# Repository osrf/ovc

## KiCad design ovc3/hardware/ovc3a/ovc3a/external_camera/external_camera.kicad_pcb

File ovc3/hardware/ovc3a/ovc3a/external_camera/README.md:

# Lens holders
Lens holders have 20mm spacing. There are various options that work fine.
We have used PT-LH010M from m12lenses.com with good results:
https://www.m12lenses.com/CNC-Machined-M12-Lens-Holder-Metal-p/pt-lh010m.htm

# FFC jumpers
The required length of jumper depends on how the external-camera board is
mounted with respect to the main OVC3 board. We have used Molex 15266-0281
for 6" length (about 150mm) but many other alternatives are possible.

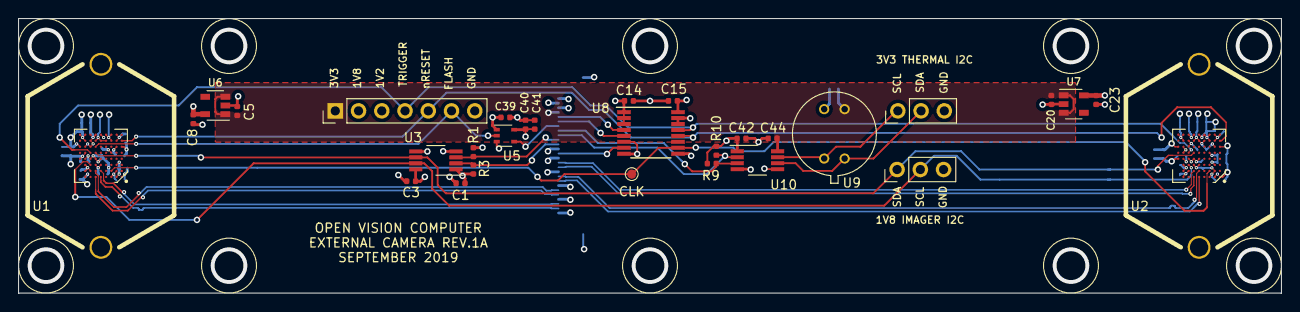
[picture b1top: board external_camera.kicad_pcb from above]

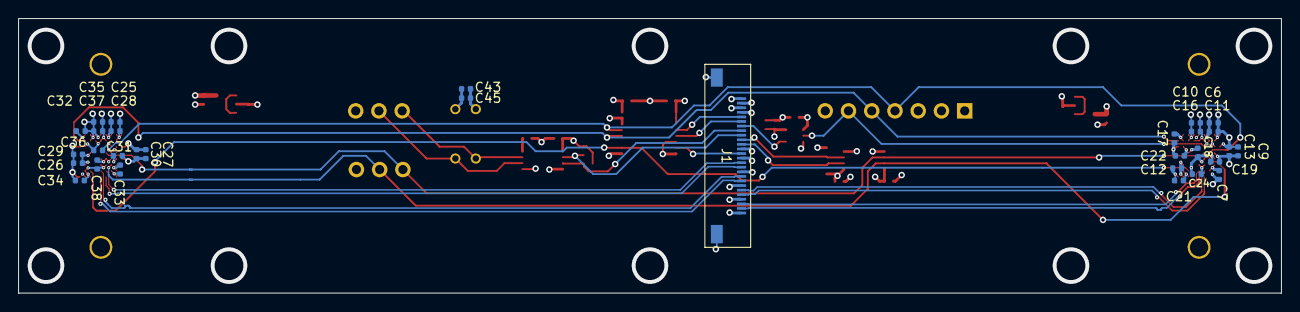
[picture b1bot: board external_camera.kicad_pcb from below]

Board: 6 copper layers, 138.0 x 30.0 mm, 63 parts (31 on the bottom side), 30 nets.

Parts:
C1, C3, C11, C12, C13, C14, C15, C16, C17, C18, C19, C21, C22, C24, C28, C29, C30, C32, C33, C34, C35, C36, C37, C38, C39, C40, C42, C43, C44: 100n; C_0402_1005Metric
C5, C8, C20, C23, C45: 1u; C_0402_1005Metric
C6, C7, C9, C10, C25, C26, C27, C31, C41: 10u; C_0402_1005Metric
J1: FFC; MOLEX_505110_2691
J2, J3: DNP; LENS_HOLDER_20MM_PT-LH010M
J4: DNP; PinHeader_1x07_P2.54mm_Vertical
J5, J6: DNP; PinHeader_1x03_P2.54mm_Vertical
R1, R3: 2k2; R_0402_1005Metric
R9, R10: DNP; R_0402_1005Metric
TP1: DNP; TestPoint_Pad_D1.0mm
U1, U2: AR0144CS; BGA-72_9x8_5.545x5.565mm
U3, U10: TCA9803; VSSOP-8_3.0x3.0mm_P0.65mm
U5: SN74AUP1T34DCK; SOT-353_SC-70-5
U6, U7: LP5907MFX-2.8; SOT-23-5
U8: SN74AXC4T245PWR; TSSOP-16_4.4x5mm_P0.65mm
U9: DNP; Melexis_TO-39

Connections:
+1V2: C1.1, C10.1, C14.1, C16.1, C19.1, C21.1, C22.1, C24.1, C31.1, C34.1, C35.1, C36.1, C37.1, C38.1, C40.1, C41.1, C42.1, J1.2, J4.3, R1.1, R3.1, R9.1, R10.1, U1.A3, U1.B2, U1.C5, U1.C6, U1.D8, U1.F2, U1.G4, U1.G5, U1.G6, U2.A3, U2.B2, U2.C5, U2.C6, U2.D8, U2.F2, U2.G4, U2.G5, U2.G6, U3.1, U3.5, U5.5, U8.1, U8.2, U8.3, U10.1, U10.5
+1V8: C3.1, C7.1, C12.1, C15.1, C18.1, C26.1, C29.1, C33.1, C39.1, J1.3, J4.2, U1.A2, U1.B7, U1.B8, U1.C2, U1.C8, U1.E3, U2.A2, U2.B8, U2.C2, U2.C8, U2.E3, U3.8, U5.1, U8.16
+3V3: C5.1, C20.1, C43.1, C44.1, C45.1, J1.4, J4.1, U6.1, U6.3, U7.1, U7.3, U9.2, U10.8
/CAM0_2V8: C6.1, C8.1, C9.1, C11.1, C13.1, C17.1, U1.F9, U1.G2, U1.G8, U1.H1, U1.H2, U1.H8, U1.H9, U6.5
/CAM1_2V8: C23.1, C25.1, C27.1, C28.1, C30.1, C32.1, U2.F9, U2.G2, U2.G8, U2.H1, U2.H2, U2.H8, U2.H9, U7.5
/EXTCLK_1V2: J1.13, U8.7
/EXTCLK_1V8: TP1.1, U1.B3, U2.B3, U8.10
/FLASH_1V2: J1.7, U5.4
/FLASH_1V8: J4.6, U1.F6, U5.2
/MIPI_CLK0+: J1.25, U1.A5
/MIPI_CLK0-: J1.24, U1.B5
/MIPI_CLK1+: J1.19, U2.A5
/MIPI_CLK1-: J1.18, U2.B5
/MIPI_DAT0+: J1.22, U1.A6
/MIPI_DAT0-: J1.21, U1.B6
/MIPI_DAT1+: J1.16, U2.A6
/MIPI_DAT1-: J1.15, U2.B6
/RESET_1V2: J1.6, U8.5
/RESET_1V8: J4.5, U1.G1, U2.G1, U8.12
/SCL0_1V2: J1.11, R3.2, U3.2
/SCL0_1V8: J5.2, U1.C7, U2.C7, U3.7
/SCL1_1V2: J1.9, R10.2, U10.2
/SCL1_3V3: J6.1, U9.4, U10.7
/SDA0_1V2: J1.10, R1.2, U3.3
/SDA0_1V8: J5.1, U1.E6, U2.E6, U3.6
/SDA1_1V2: J1.8, R9.2, U10.3
/SDA1_3V3: J6.2, U9.1, U10.6
/TRIGGER_1V2: J1.5, U8.4
/TRIGGER_1V8: J4.4, U1.E7, U2.E7, U8.13
GND: C1.2, C3.2, C5.2, C6.2, C7.2, C8.2, C9.2, C10.2, C11.2, C12.2, C13.2, C14.2, C15.2, C16.2, C17.2, C18.2, C19.2, C20.2, C21.2, C22.2, C23.2, C24.2, C25.2, C26.2, C27.2, C28.2, C29.2, C30.2, C31.2, C32.2, C33.2, C34.2, C35.2, C36.2, C37.2, C38.2, C39.2, C40.2, C41.2, C42.2, C43.2, C44.2, C45.2, J1.1, J1.12, J1.14, J1.17, J1.20, J1.23, J1.26, J1.27, J2.1, J3.1, J4.7, J5.3, J6.3, U1.A1, U1.A8, U1.D5, U1.D6, U1.D7, U1.D9, U1.E8, U1.F1, U1.F7, U1.F8, U1.G3, U1.G7, U1.H3, U1.H4, U1.H5, U1.H6, U1.H7, U2.A1, U2.A8, U2.B7, U2.D5, U2.D6, U2.D7, U2.D9, U2.E8, U2.F1, U2.F7, U2.F8, U2.G3, U2.G7, U2.H3, U2.H4, U2.H5, U2.H6, U2.H7, U3.4, U5.3, U6.2, U7.2, U8.6, U8.8, U8.9, U8.14, U8.15, U9.3, U10.4

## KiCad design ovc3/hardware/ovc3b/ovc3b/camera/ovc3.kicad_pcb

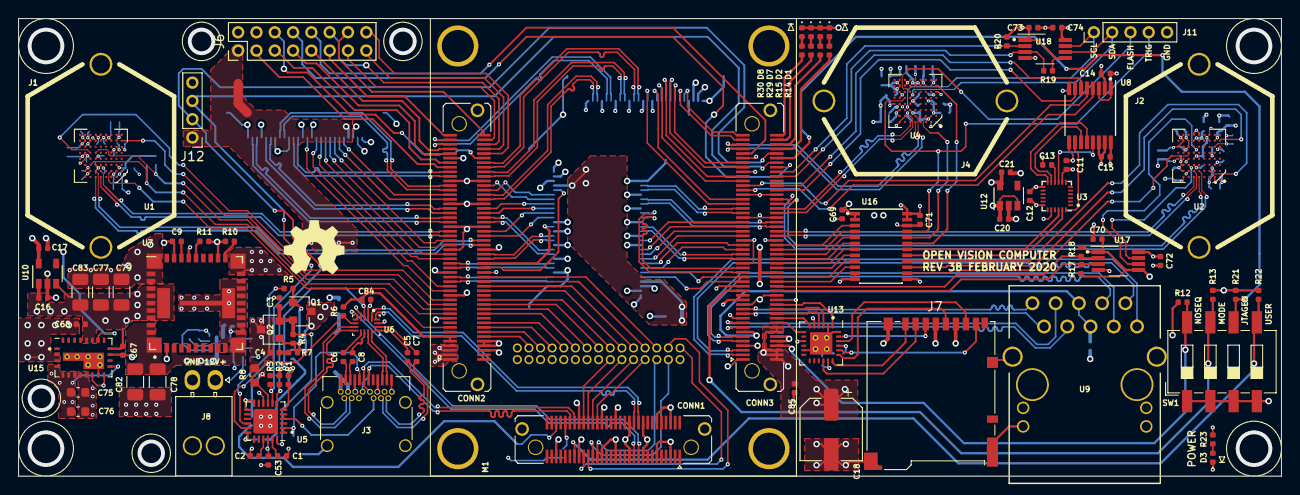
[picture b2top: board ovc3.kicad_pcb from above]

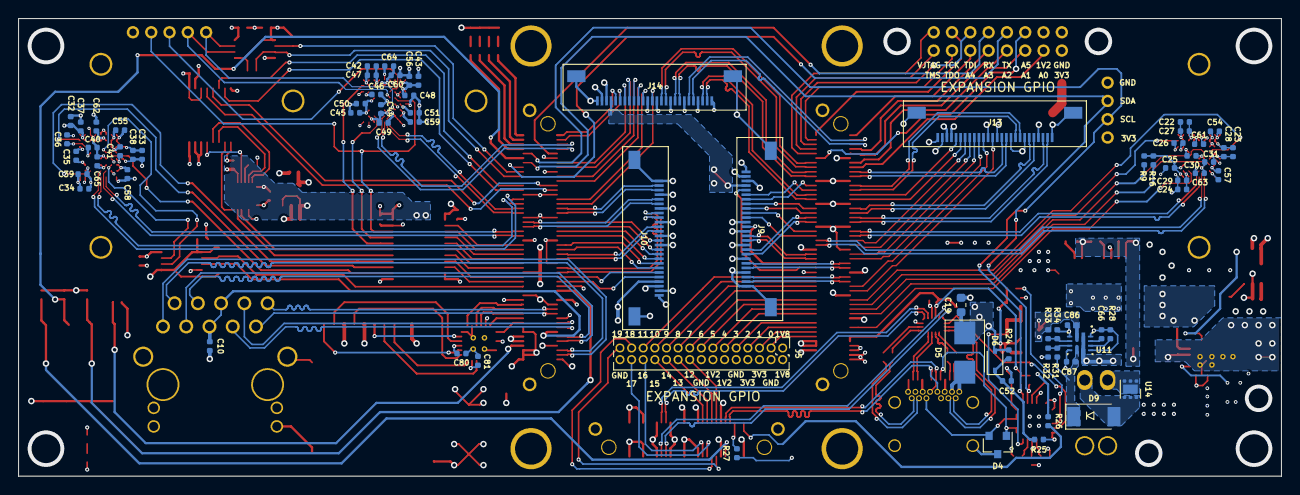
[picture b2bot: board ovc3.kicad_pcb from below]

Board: 6 copper layers, 138.0 x 50.0 mm, 167 parts (72 on the bottom side), 238 nets.

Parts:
C1, C2, C3, C16, C17, C20, C21, C52, C67: 1u; C_0402_1005Metric
C4, C5, C6, C7, C8, C10, C11, C12, C13, C14, C15, C26, C27, C28, C29, C30, C31, C36, C37, C38, C39, C40, C41, C44, C47, C48, C49, C50, C51, C53, C54, C55, C56, C57, C58, C59, C60, C61, C62, C63, C64, C65, C66, C69, C70, C71, C72, C73, C74, C80, C81, C84, C85, C86, C87: 100n; C_0402_1005Metric
C9: 3n3; C_0402_1005Metric
C18: 680u; CP_Elec_6.3x7.7
C19: 4u7; C_0603_1608Metric
C22, C23, C24, C25, C32, C33, C34, C35, C42, C43, C45, C46, C68: 10u; C_0402_1005Metric
C75, C76: 22u; C_0603_1608Metric
C77: 100u; C_1206_3216Metric
C78, C82: 22u; C_1206_3216Metric
C79, C83: 47u; C_1206_3216Metric
D1, D2, D3, D7, D8: LED; LED_0402_1005Metric
D4: ESD7002WTT1G; SOT-23
D5: SMBJ22A; D_SMB
D6: SDMK0340L-7-F; D_SOD-323
D9: PMEG3030EP,115; D_SOD-128
J1: LEFT_LENS; LENS_HOLDER_20MM_PT-LH010M
J2: RIGHT_LENS; LENS_HOLDER_20MM_PT-LH010M
J3: USB_C_Receptacle; USB_C_Receptacle_Wurth_632723300011
J4: MIDDLE_LENS; LENS_HOLDER_20MM_PT-LH010M
J5: LOW_SPEED_EXP; PinHeader_2x15_P1.27mm_Vertical
J6: FRONT_PACK; PinHeader_2x08_P2.00mm_Vertical
J7: Micro_SD_Card_Det_Hirose_DM3BT; microSD_HC_Hirose_DM3BT-DSF-PEJS
J8: AUX_PWR; Molex_Nano-Fit_105313-xx02_1x02_P2.50mm_Horizontal
J9: BONUS1; MOLEX_505110_2691
J10: BONUS2; MOLEX_505110_2691
J11: CAM2_TIMING_DEBUG; PinHeader_1x05_P2.00mm_Vertical
J12: I2C_DEBUG; PinHeader_1x04_P2.00mm_Vertical
J13: BONUS3; MOLEX_505110_2691
J14: BONUS4; MOLEX_505110_2691
LOGO1: Logo_Open_Hardware_Small; OSHW-Symbol_6.7x6mm_SilkScreen
M1: TE0820
Q1, Q2: SI2369DS; SOT-23
R1, R4, R6: 100k; R_0402_1005Metric
R2, R3, R12, R13, R21, R22, R26, R32, R34: 10k; R_0402_1005Metric
R5, R28: 22k; R_0402_1005Metric
R7: 100R; R_0402_1005Metric
R8: 1k; R_0603_1608Metric
R9, R16, R17, R18, R19, R20: 2k2; R_0402_1005Metric
R10: 90k9; R_0402_1005Metric
R11: 316R; R_0402_1005Metric
R14, R15, R23, R29, R30: 330R; R_0402_1005Metric
R24: 470; R_0402_1005Metric
R25, R27: 1k; R_0402_1005Metric
R31, R33: 143k; R_0402_1005Metric
SW1: SW_DIP_x04; SW_DIP_SPSTx04_Slide_6.7x11.72mm_W8.61mm_P2.54mm_LowProfile
U1, U2, U4: AR0144CS; BGA-72_9x8_5.545x5.565mm
U3: ICM-20948; InvenSense_QFN-24_3x3mm_P0.4mm
U5: STUSB4500; QFN-24-1EP_4x4mm_P0.5mm_EP2.7x2.7mm
U6: HD3SS3202; TI_R_PUQFN_N16
U7: LMZ31707; TI_RVQ_42
U8: SN74AXC4T245; TSSOP-16_4.4x5mm_P0.65mm
U9: ARJ11C-MBSAS-A-BA-7MU2
U10, U12: LP5907MFX-2.8; SOT-23-5
U11: TPS2121; Texas_VQFN-HR-12_2x2.5_Pitch0.5mm
U13: TXS02612; TI_RTW0024B
U14: TVS1800DRV; WSON-6-1EP_2x2mm_P0.65mm_EP1x1.6mm
U15: EN5322QI; Converter_DCDC_Intel_QFN-24_4x6mm_P0.65mm_ThermalVias
U16: SN74AXCH8T245; TSSOP-24_4.4x7.8mm_P0.65mm
U17, U18: TCA9803; VSSOP-8_3.0x3.0mm_P0.65mm

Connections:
3V3_VOUT: C84.2, M1.JB2.9, M1.JB2.11, R2.1, R3.1, R6.1, U6.3
+1V2: C14.1, C24.1, C26.1, C29.1, C31.1, C34.1, C36.1, C39.1, C41.1, C44.1, C46.1, C49.1, C51.1, C60.1, C61.1, C62.1, C63.1, C64.1, C65.1, C69.1, C70.1, C73.1, C75.1, C76.1, J5.12, J5.14, J6.4, J9.25, J10.25, J13.25, J14.25, M1.JB1.10, M1.JB1.12, M1.JB2.8, M1.JB2.10, R17.1, R18.1, R19.1, R20.1, U1.A3, U1.B2, U1.C5, U1.C6, U1.D8, U1.F2, U1.G4, U1.G5, U1.G6, U2.A3, U2.B2, U2.C5, U2.C6, U2.D8, U2.F2, U2.G4, U2.G5, U2.G6, U4.A3, U4.B2, U4.C5, U4.C6, U4.D8, U4.F2, U4.G4, U4.G5, U4.G6, U8.1, U8.3, U15.4, U15.5, U15.6, U15.7, U15.13, U16.1, U16.2, U17.1, U17.5, U18.1, U18.5
+1V8: C11.1, C15.1, C25.1, C30.1, C35.1, C40.1, C45.1, C50.1, C57.1, C58.1, C59.1, C71.1, C72.1, C74.1, J5.1, J5.2, J9.24, J10.24, J13.24, J14.24, M1.JB1.40, M1.JB2.6, R9.1, R13.1, R16.1, R21.1, R22.1, U1.A2, U1.B8, U1.C2, U1.C8, U1.E3, U2.A2, U2.B8, U2.C2, U2.C8, U2.E3, U3.8, U4.A2, U4.B8, U4.C2, U4.C8, U4.E3, U8.16, U15.18, U16.23, U16.24, U17.8, U18.8
+3V3: C12.1, C16.1, C18.1, C20.1, C53.1, C67.1, C68.1, C77.1, C79.1, C80.1, C81.1, C83.1, C85.1, J5.6, J5.8, J6.1, J7.4, J9.23, J10.23, J12.1, J13.23, J14.23, M1.JB1.2, M1.JB1.4, M1.JB1.6, M1.JB1.14, M1.JB1.16, M1.JB1.27, M1.JB2.1, M1.JB2.3, M1.JB2.5, M1.JB2.7, R12.1, R23.1, R27.1, U3.13, U5.22, U7.27, U7.34, U7.35, U7.36, U7.37, U7.38, U7.41, U10.1, U10.3, U12.1, U12.3, U13.5, U13.17, U13.21, U15.10, U15.12, U15.16, U15.19, U15.20
/imagers/CAM0_2V8: C17.1, C22.1, C23.1, C27.1, C28.1, C54.1, U1.F9, U1.G2, U1.G8, U1.H1, U1.H2, U1.H8, U1.H9, U10.5
/imagers/CAM1_2V8: C21.1, C32.1, C33.1, C37.1, C38.1, C42.1, C43.1, C47.1, C48.1, C55.1, C56.1, U2.F9, U2.G2, U2.G8, U2.H1, U2.H2, U2.H8, U2.H9, U4.F9, U4.G2, U4.G8, U4.H1, U4.H2, U4.H8, U4.H9, U12.5
/misc/LS_CLK: J7.5, U13.19
/misc/LS_CMD: J7.3, U13.23
/misc/LS_DAT0: J7.7, U13.22
/misc/LS_DAT1: J7.8, U13.20
/misc/LS_DAT2: J7.1, U13.18
/misc/LS_DAT3: J7.2, U13.16
/te0820/CAM1_EXTCLK_1V2: M1.JB1.42, U16.8
/te0820/CAM1_SCL_1V2: M1.JB1.34, R18.2, U17.2
/te0820/CAM1_SDA_1V2: M1.JB1.32, R17.2, U17.3
/te0820/CAM1_TRIG_1V2: M1.JB1.36, U16.10
/te0820/CAM1_nRESET_1V2: M1.JB1.38, U16.9
/te0820/CAM2_EXTCLK_1V2: M1.JB1.50, U16.4
/te0820/CAM2_SCL_1V2: M1.JB1.84, R20.2, U18.2
/te0820/CAM2_SDA_1V2: M1.JB1.82, R19.2, U18.3
/te0820/CAM2_TRIG_1V2: M1.JB1.52, U16.3
/te0820/CAM2_nRESET_1V2: M1.JB1.48, U16.5
/te0820/DIPSWITCH: M1.JB3.47, R22.2, SW1.5
/te0820/ICM_IMU_INT1_1V2: M1.JB1.77, U8.5
/te0820/ICM_SPI_CLK_1V2: M1.JB1.44, U16.7
/te0820/ICM_SPI_CS_1V2: M1.JB1.46, U16.6
/te0820/ICM_SPI_MISO_1V2: M1.JB1.75, U8.4
/te0820/ICM_SPI_MOSI_1V2: M1.JB1.76, U8.7
/te0820/ICM_SPI_SYNC_1V2: M1.JB1.78, U8.6
/te0820/JTAGEN: M1.JB1.90, R21.2, SW1.6
/te0820/MODE: M1.JB1.31, R13.2, SW1.7
/te0820/NOSEQ: M1.JB1.8, R12.2, SW1.8
/usb3/1V2: C2.1, U5.21
/usb3/2V7: C1.1, U5.23
/usb3/ABSIDE: R6.2, U5.17, U6.6
/usb3/AUX_PWR: D9.2, J8.1, U14.4, U14.5, U14.6
/usb3/CONN_CC1: D4.1, J3.A5, U5.1, U5.2
/usb3/CONN_CC2: D4.2, J3.B5, U5.4, U5.5
/usb3/CONN_RX1+: J3.B11, U6.8
/usb3/CONN_RX1-: J3.B10, U6.7
/usb3/CONN_RX2+: J3.A11, U6.12
/usb3/CONN_RX2-: J3.A10, U6.11
/usb3/CONN_TX1+: C6.2, J3.A2
/usb3/CONN_TX1-: C8.2, J3.A3
/usb3/CONN_TX2+: C5.2, J3.B2
/usb3/CONN_TX2-: C7.2, J3.B3
/usb3/CONN_VBUS: C19.1, D5.1, D6.2, J3.A4, J3.A9, J3.B4, J3.B9, Q1.3, R24.1
/usb3/DISCH: R8.2, U5.9
/usb3/GATES: Q1.1, Q2.1, R4.2, R5.1, R7.2
/usb3/PH: U7.10, U7.13, U7.14, U7.15, U7.16, U7.17, U7.18, U7.19, U7.42
/usb3/PWGND: C9.2, R10.2, R11.2, U7.2, U7.23, U7.29
/usb3/RESET: R1.1, U5.6
/usb3/T1+: C6.1, U6.9
/usb3/T1-: C8.1, U6.10
/usb3/T2+: C5.1, U6.13
/usb3/T2-: C7.1, U6.14
/usb3/VAUX: C87.1, D9.1, R31.1, U11.7
BONUS1_CLK0+: J9.2, M1.JB2.35
BONUS1_CLK0-: J9.3, M1.JB2.37
BONUS1_CLK1+: J9.8, M1.JB2.62
BONUS1_CLK1-: J9.9, M1.JB2.64
BONUS1_DAT0+: J9.5, M1.JB2.41
BONUS1_DAT0-: J9.6, M1.JB2.43
BONUS1_DAT1+: J9.11, M1.JB2.46
BONUS1_DAT1-: J9.12, M1.JB2.48
BONUS1_EXTCLK: J9.14, M1.JB2.44
BONUS1_FLASH: J9.20, M1.JB2.78
BONUS1_RESET: J9.21, M1.JB2.76
BONUS1_SCL0: J9.16, M1.JB2.56
BONUS1_SCL1: J9.18, M1.JB2.66
BONUS1_SDA0: J9.17, M1.JB2.58
BONUS1_SDA1: J9.19, M1.JB2.68
BONUS1_TRIGGER: J9.22, M1.JB2.42
BONUS2_CLK0+: J10.2, M1.JB1.67
BONUS2_CLK0-: J10.3, M1.JB1.65
BONUS2_CLK1+: J10.8, M1.JB1.39
BONUS2_CLK1-: J10.9, M1.JB1.41
BONUS2_DAT0+: J10.5, M1.JB1.62
BONUS2_DAT0-: J10.6, M1.JB1.60
BONUS2_DAT1+: J10.11, M1.JB1.47
BONUS2_DAT1-: J10.12, M1.JB1.45
BONUS2_EXTCLK: J10.14, M1.JB1.61
BONUS2_FLASH: J10.20, M1.JB1.49
BONUS2_RESET: J10.21, M1.JB1.37
BONUS2_SCL0: J10.16, M1.JB1.59
BONUS2_SCL1: J10.18, M1.JB1.55
BONUS2_SDA0: J10.17, M1.JB1.57
BONUS2_SDA1: J10.19, M1.JB1.51
BONUS2_TRIGGER: J10.22, M1.JB1.35
BONUS3_CLK0+: J13.2, M1.JB2.61
BONUS3_CLK0-: J13.3, M1.JB2.63
BONUS3_CLK1+: J13.8, M1.JB2.77
BONUS3_CLK1-: J13.9, M1.JB2.75
BONUS3_DAT0+: J13.5, M1.JB2.65
BONUS3_DAT0-: J13.6, M1.JB2.67
BONUS3_DAT1+: J13.11, M1.JB2.81
BONUS3_DAT1-: J13.12, M1.JB2.83
BONUS3_EXTCLK: J13.14, M1.JB2.31
BONUS3_FLASH: J13.20, M1.JB2.53
BONUS3_RESET: J13.21, M1.JB2.71
BONUS3_SCL0: J13.16, M1.JB2.33
BONUS3_SCL1: J13.18, M1.JB2.47
BONUS3_SDA0: J13.17, M1.JB2.45
BONUS3_SDA1: J13.19, M1.JB2.51
BONUS3_TRIGGER: J13.22, M1.JB2.73
BONUS4_CLK0+: J14.2, M1.JB2.72
BONUS4_CLK0-: J14.3, M1.JB2.74
BONUS4_CLK1+: J14.8, M1.JB2.82
BONUS4_CLK1-: J14.9, M1.JB2.84
BONUS4_DAT0+: J14.5, M1.JB2.95
BONUS4_DAT0-: J14.6, M1.JB2.97
BONUS4_DAT1+: J14.11, M1.JB2.86
BONUS4_DAT1-: J14.12, M1.JB2.88
BONUS4_EXTCLK: J14.14, M1.JB1.69
BONUS4_FLASH: J14.20, M1.JB1.87
BONUS4_RESET: J14.21, M1.JB1.97
BONUS4_SCL0: J14.16, M1.JB1.71
BONUS4_SCL1: J14.18, M1.JB1.81
BONUS4_SDA0: J14.17, M1.JB1.79
BONUS4_SDA1: J14.19, M1.JB1.85
BONUS4_TRIGGER: J14.22, M1.JB1.99
CAM0_CLK+: M1.JB2.55, U1.A5
CAM0_CLK-: M1.JB2.57, U1.B5
CAM0_D0+: M1.JB2.52, U1.A6
CAM0_D0-: M1.JB2.54, U1.B6
CAM0_EXTCLK_1V8: M1.JB2.15, U1.B3
CAM0_SCL_1V8: M1.JB2.21, R16.2, U1.C7
CAM0_SDA_1V8: M1.JB2.23, R9.2, U1.E6
CAM0_TRIG_1V8: M1.JB2.27, U1.E7
CAM0_nRESET_1V8: M1.JB2.25, U1.G1
CAM1_CLK+: M1.JB1.70, U2.A5
CAM1_CLK-: M1.JB1.72, U2.B5
CAM1_D0+: M1.JB1.58, U2.A6
CAM1_D0-: M1.JB1.56, U2.B6
CAM1_EXTCLK_1V8: U2.B3, U16.16
CAM1_SCL_1V8: U2.C7, U17.7
CAM1_SDA_1V8: U2.E6, U17.6
CAM1_TRIG_1V8: U2.E7, U16.14
CAM1_nRESET_1V8: U2.G1, U16.15
CAM2_CLK+: M1.JB1.95, U4.A5
CAM2_CLK-: M1.JB1.93, U4.B5
CAM2_D0+: M1.JB1.68, U4.A6
CAM2_D0-: M1.JB1.66, U4.B6
CAM2_EXTCLK_1V8: U4.B3, U16.20
CAM2_FLASH_1V8: J11.3, U4.F6
CAM2_SCL_1V8: J11.1, U4.C7, U18.7
CAM2_SDA_1V8: J11.2, U4.E6, U18.6
CAM2_TRIG_1V8: J11.4, U4.E7, U16.21
CAM2_nRESET_1V8: U4.G1, U16.19
ETH_VCC: C10.1, M1.JB1.13, U9.5, U9.6
FRONT_AUX0: J6.3, M1.JB2.85
FRONT_AUX1: J6.5, M1.JB2.87
FRONT_AUX2: J6.7, M1.JB2.91
FRONT_AUX3: J6.9, M1.JB2.93
FRONT_AUX4: J6.11, M1.JB2.99
FRONT_AUX5: J6.6, M1.JB2.90
GND: C1.2, C2.2, C3.2, C10.2, C11.2, C12.2, C13.2, C14.2, C15.2, C16.2, C17.2, C18.2, C19.2, C20.2, C21.2, C22.2, C23.2, C24.2, C25.2, C26.2, C27.2, C28.2, C29.2, C30.2, C31.2, C32.2, C33.2, C34.2, C35.2, C36.2, C37.2, C38.2, C39.2, C40.2, C41.2, C42.2, C43.2, C44.2, C45.2, C46.2, C47.2, C48.2, C49.2, C50.2, C51.2, C52.2, C53.2, C54.2, C55.2, C56.2, C57.2, C58.2, C59.2, C60.2, C61.2, C62.2, C63.2, C64.2, C65.2, C66.2, C67.2, C68.2, C69.2, C70.2, C71.2, C72.2, C73.2, C74.2, C75.2, C76.2, C77.2, C78.2, C79.2, C80.2, C81.2, C82.2, C83.2, C84.1, C85.2, C86.2, C87.2, D1.1, D2.1, D3.1, D4.3, D5.2, D7.1, D8.1, J1.1, J2.1, J3.A1, J3.A12, J3.B1, J3.B12, J3.S1, J4.1, J5.4, J5.10, J5.16, J5.30, J6.2, J7.6, J7.11, J8.2, J9.1, J9.4, J9.7, J9.10, J9.13, J9.15, J9.26, J9.27, J10.1, J10.4, J10.7, J10.10, J10.13, J10.15, J10.26, J10.27, J11.5, J12.4, J13.1, J13.4, J13.7, J13.10, J13.13, J13.15, J13.26, J13.27, J14.1, J14.4, J14.7, J14.10, J14.13, J14.15, J14.26, J14.27, M1.JB1.1, M1.JB1.7, M1.JB1.19, M1.JB1.25, M1.JB1.30, M1.JB1.33, M1.JB1.43, M1.JB1.53, M1.JB1.54, M1.JB1.63, M1.JB1.64, M1.JB1.73, M1.JB1.74, M1.JB1.83, M1.JB1.89, M1.JB2.19, M1.JB2.29, M1.JB2.39, M1.JB2.40, M1.JB2.49, M1.JB2.50, M1.JB2.59, M1.JB2.60, M1.JB2.69, M1.JB2.70, M1.JB2.79, M1.JB2.80, M1.JB2.89, M1.JB3.5, M1.JB3.6, M1.JB3.11, M1.JB3.12, M1.JB3.17, M1.JB3.18, M1.JB3.23, M1.JB3.24, M1.JB3.29, M1.JB3.30, M1.JB3.35, M1.JB3.36, M1.JB3.45, M1.JB3.46, M1.JB3.55, R1.2, R28.2, R32.2, R34.2, SW1.1, SW1.2, SW1.3, SW1.4, U1.A1, U1.A8, U1.B7, U1.D5, U1.D6, U1.D7, U1.D9, U1.E8, U1.F1, U1.F7, U1.F8, U1.G3, U1.G7, U1.H3, U1.H4, U1.H5, U1.H6, U1.H7, U2.A1, U2.A8, U2.B7, U2.D5, U2.D6, U2.D7, U2.D9, U2.E8, U2.F1, U2.F7, U2.F8, U2.G3, U2.G7, U2.H3, U2.H4, U2.H5, U2.H6, U2.H7, U3.18, U3.20, U4.A1, U4.A8, U4.B7, U4.D5, U4.D6, U4.D7, U4.D9, U4.E8, U4.F1, U4.F7, U4.F8, U4.G3, U4.G7, U4.H3, U4.H4, U4.H5, U4.H6, U4.H7, U5.10, U5.12, U5.13, U5.25, U6.2, U6.15, U7.20, U7.21, U7.31, U7.32, U7.33, U8.2, U8.8, U8.9, U8.14, U8.15, U9.11, U9.14, U9.MNT, U9.SHLD, U10.2, U11.3, U11.6, U11.9, U11.12, U12.2, U13.2, U13.11, U13.24, U13.25, U14.1, U14.2, U14.3, U14.7, U15.2, U15.3, U15.8, U15.9, U15.11, U15.15, U15.25, U16.11, U16.12, U16.13, U16.22, U17.4, U18.4
GPIO0: J5.3, M1.JB2.12
GPIO1: J5.5, M1.JB2.14
GPIO2: J5.7, M1.JB2.16
GPIO3: J5.9, M1.JB2.18
GPIO4: J5.11, M1.JB2.22
GPIO5: J5.13, M1.JB2.24
GPIO6: J5.15, M1.JB2.26
GPIO7: J5.17, M1.JB2.28
GPIO8: J5.19, M1.JB2.32
GPIO9: J5.21, M1.JB2.34
GPIO10: J5.23, M1.JB2.36
GPIO11: J5.25, M1.JB2.38
GPIO12: J5.18, M1.JB3.44
GPIO13: J5.20, M1.JB3.42
GPIO14: J5.22, M1.JB3.40
GPIO15: J5.24, M1.JB3.38
GPIO16: J5.26, M1.JB3.37
GPIO17: J5.28, M1.JB3.39
GPIO18: J5.27, M1.JB3.41
GPIO19: J5.29, M1.JB3.43
ICM_IMU_INT1_1V8: U3.12, U8.12
ICM_IMU_SYNC_1V8: U3.11, U8.11
ICM_SPI_CLK_1V8: U3.23, U16.17
ICM_SPI_CS_1V8: U3.22, U16.18
ICM_SPI_MISO_1V8: U3.9, U8.13
ICM_SPI_MOSI_1V8: U3.24, U8.10
JTAG_TCK: J6.14, M1.JB2.100
JTAG_TDI: J6.12, M1.JB2.96
JTAG_TDO: J6.13, M1.JB2.98
JTAG_TMS: J6.15, M1.JB2.94
LED0: M1.JB1.94, R14.2
LED1: M1.JB1.96, R15.2
LED2: M1.JB1.98, R29.2
LED3: M1.JB1.100, R30.2
unnamed: C3.1, Q1.2, Q2.2, R4.1, U5.24
unnamed: C4.2, R7.1
unnamed: C9.1, U7.28
unnamed: C13.1, U3.10
unnamed: C52.1, D6.1, R24.2, R25.1
unnamed: C66.1, U11.11
unnamed: D1.2, R14.1
unnamed: D2.2, R15.1
unnamed: D3.2, R23.2
unnamed: D7.2, R29.1
unnamed: D8.2, R30.1
unnamed: M1.JB3.52, R27.2
unnamed: M1.JB3.56, R26.2
unnamed: R5.2, U5.16
unnamed: R10.1, U7.22
unnamed: R11.1, U7.26
unnamed: R25.2, U5.18
unnamed: R28.1, U11.10
unnamed: R31.2, R32.1, U11.5
unnamed: R33.2, R34.1, U11.4
PHY_MDI0_N: M1.JB1.5, U9.2
PHY_MDI0_P: M1.JB1.3, U9.1
PHY_MDI1_N: M1.JB1.11, U9.4
PHY_MDI1_P: M1.JB1.9, U9.3
PHY_MDI2_N: M1.JB1.17, U9.8
PHY_MDI2_P: M1.JB1.15, U9.7
PHY_MDI3_N: M1.JB1.23, U9.10
PHY_MDI3_P: M1.JB1.21, U9.9
ROOT_RX: J6.10, M1.JB1.91
ROOT_TX: J6.8, M1.JB1.86
SD_CLK: M1.JB1.28, U13.9
SD_CMD: M1.JB1.26, U13.1
SD_DAT0: M1.JB1.24, U13.3
SD_DAT1: M1.JB1.22, U13.4
SD_DAT2: M1.JB1.20, U13.6
SD_DAT3: M1.JB1.18, U13.7
USB2_D+: J3.A6, J3.B6, M1.JB3.48
USB2_D-: J3.A7, J3.B7, M1.JB3.50
USB3_RX+: M1.JB3.19, U6.4
USB3_RX-: M1.JB3.21, U6.5
USB3_TX+: M1.JB3.22, U6.16
USB3_TX-: M1.JB3.20, U6.1
USB_SCL: J12.2, M1.JB1.92, R2.2, U5.7
USB_SDA: J12.3, M1.JB1.88, R3.2, U5.8
VBUS: C4.1, C86.1, Q2.3, R8.1, R26.1, R33.1, U11.2
VCC: C78.1, C82.1, U7.1, U7.3, U7.11, U7.12, U7.39, U7.40, U11.1, U11.8
VCC_JTAG: J6.16, M1.JB2.92
